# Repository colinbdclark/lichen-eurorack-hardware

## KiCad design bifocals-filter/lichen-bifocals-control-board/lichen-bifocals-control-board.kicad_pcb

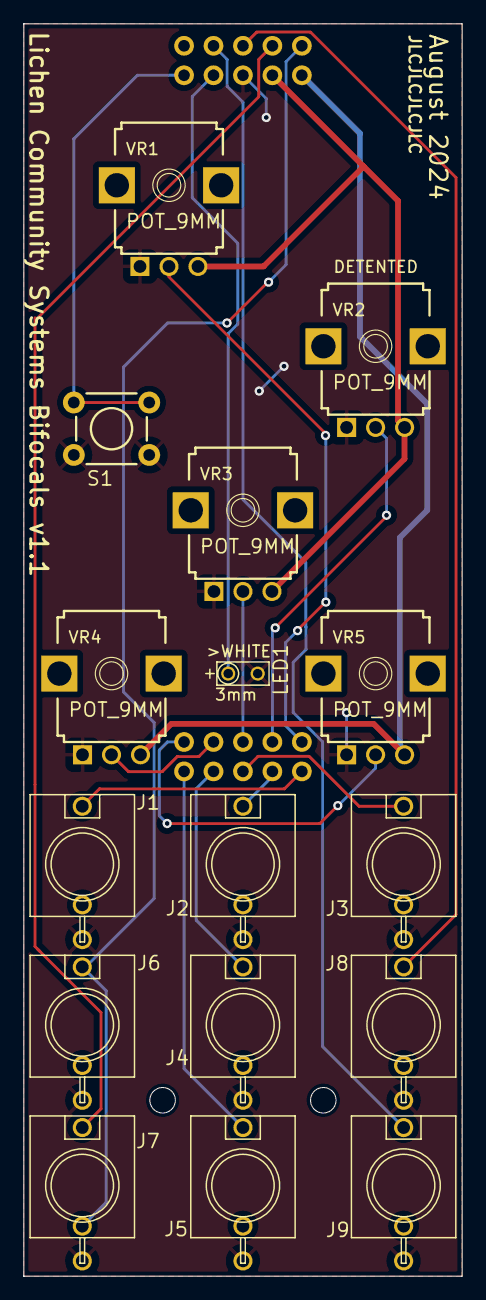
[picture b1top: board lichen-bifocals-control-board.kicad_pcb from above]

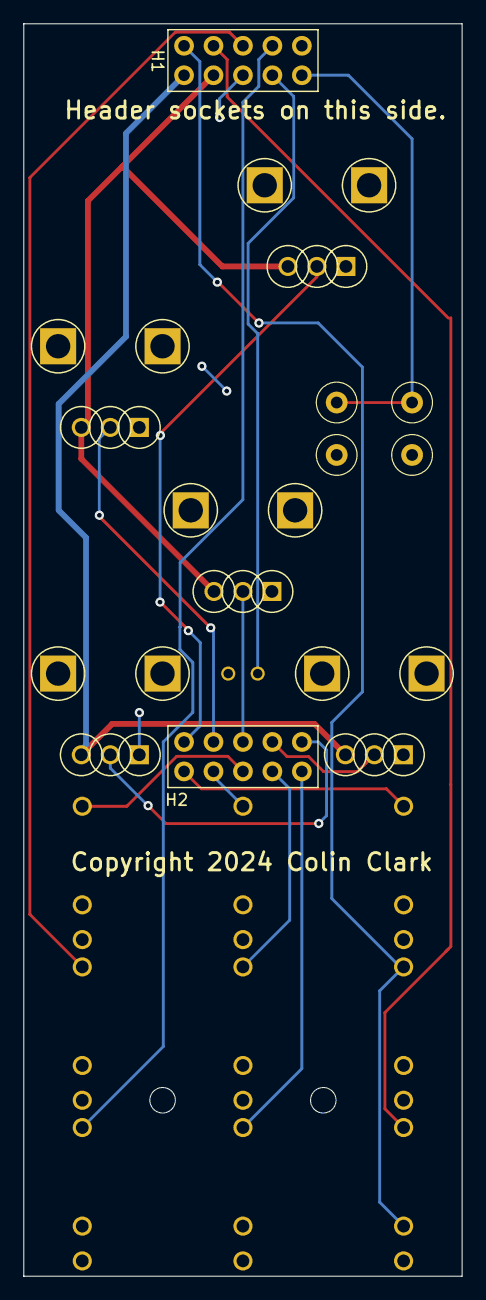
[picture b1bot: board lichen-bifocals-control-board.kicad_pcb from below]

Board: 2 copper layers, 37.8 x 108.0 mm, 20 parts (2 on the bottom side), 19 nets.

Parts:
H1, H2: PIN_HEADER_2x5; Pins_2x05_2.54mm_TH
J1, J2, J3, J4, J5, J6, J7, J8, J9: EURO_JACK; S_JACK
LED1: LED
MH2, MH2#2: MountingHole_2.2mm_M2
S1: TAC_SWITCH_PTH; TL1105SPF250Q_SILK
VR1, VR2, VR3, VR4, VR5: POT_9MM; 9MM_SNAP-IN_POT_SILK

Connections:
+3.3V: H1.1, VR4.3, VR5.3
+5V: H1.3, VR1.3, VR2.3, VR3.3
AUDIO_IN_L: H1.2, J6.TIP, J7.NORM
AUDIO_IN_R: H1.4, J7.TIP
AUDIO_OUT_L: H1.6, J8.TIP
AUDIO_OUT_R: H1.8, J9.TIP
BUTTON: H1.9, S1.1, S1.2
GND: H1.5, J1.GND, J2.GND, J3.GND, J4.GND, J5.GND, J6.GND, J7.GND, J8.GND, J9.GND, LED1.K (C), S1.3, S1.4, VR1.1, VR2.1, VR3.1, VR4.1, VR5.1
JACK_CV_1: H2.1, J1.TIP
JACK_CV_2: H2.3, J2.TIP
JACK_CV_3: H2.5, J3.TIP
JACK_CV_4: H2.7, J4.TIP
JACK_CV_5: H2.9, J5.TIP
LED_CV_OUT: H1.7, LED1.A
POT_1_CV_6: H2.2, VR1.2
POT_2_CV_7: H2.4, VR2.2
POT_3_CV_8: H2.6, VR3.2
POT_4_CV_9: H2.8, VR4.2
POT_5_CV_10: H2.10, VR5.2

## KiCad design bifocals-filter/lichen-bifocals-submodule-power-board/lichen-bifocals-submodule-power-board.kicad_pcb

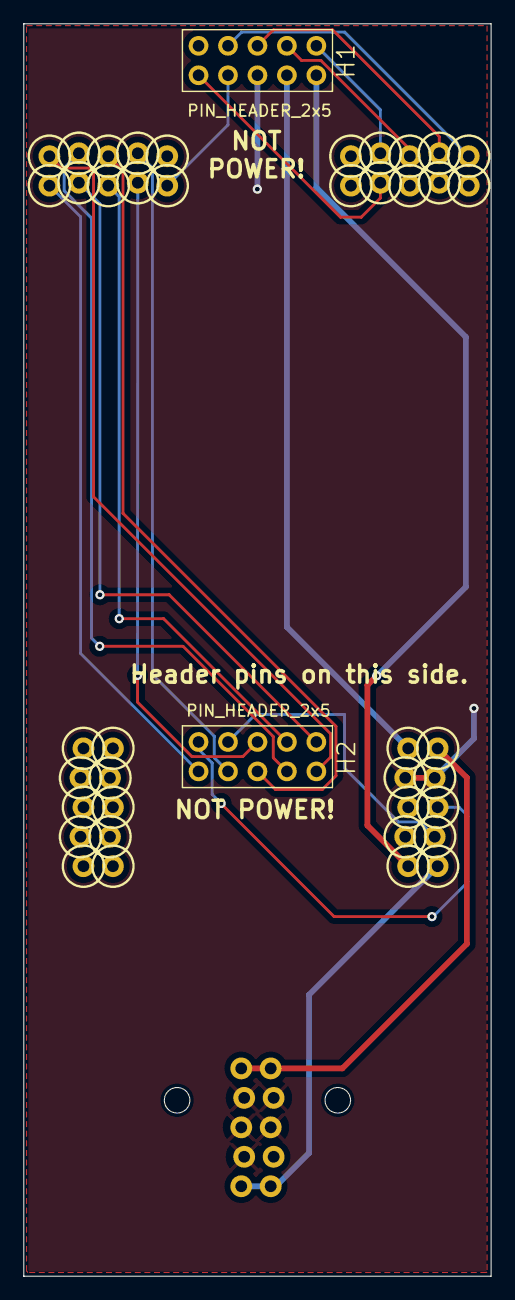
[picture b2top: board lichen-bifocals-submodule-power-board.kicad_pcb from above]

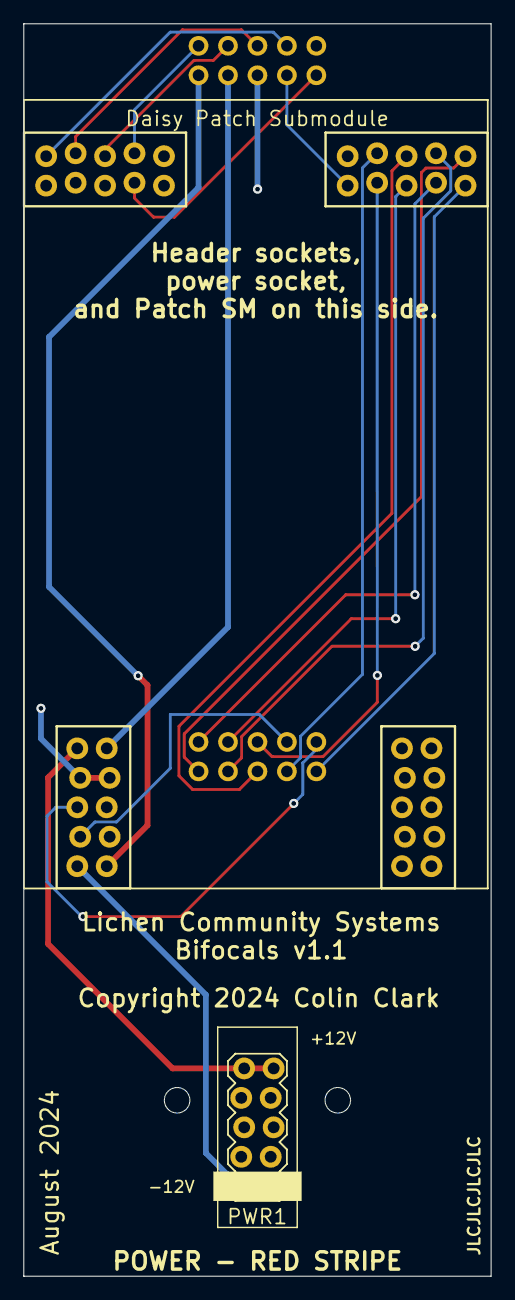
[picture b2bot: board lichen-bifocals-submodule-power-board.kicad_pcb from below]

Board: 2 copper layers, 40.3 x 108.0 mm, 6 parts (3 on the bottom side), 21 nets.

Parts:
H1, H2: PIN_HEADER_2x5; Pins_2x05_2.54mm_TH
MCU1: Daisy Patch Submodule; Daisy_Patch_Submodule
MH1, MH2: MountingHole_2.2mm_M2
PWR1: EURORACK_POWERSHROUD; EURORACK_POWER_SHROUD_LOCK

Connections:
+3.3V: H1.1, MCU1.A10 (+3V3)
+5V: H1.3, MCU1.A6 (+5V)
+12V: MCU1.A5 (+12V), PWR1.POS1, PWR1.POS2
-12V: MCU1.A1 (-12V), PWR1.NEG1, PWR1.NEG2
AUDIO_IN_L: H1.2, MCU1.B4 (AUDIO_IN_L)
AUDIO_IN_R: H1.4, MCU1.B3 (AUDIO_IN_R)
AUDIO_OUT_L: H1.6, MCU1.B2 (AUDIO_OUT_L)
AUDIO_OUT_R: H1.8, MCU1.B1 (AUDIO_OUT_R)
BUTTON: H1.9, MCU1.B7 (I2C1_SCL)
GND: H1.5, MCU1.A4 (GND), MCU1.A7 (GND), PWR1.GND1 (GND), PWR1.GND2 (GND), PWR1.GND3 (GND), PWR1.GND4 (GND), PWR1.GND5 (GND)
JACK_CV_1: H2.1, MCU1.C5 (CV1)
JACK_CV_2: H2.3, MCU1.C4 (CV2)
JACK_CV_3: H2.5, MCU1.C3 (CV3)
JACK_CV_4: H2.7, MCU1.C2 (CV4)
JACK_CV_5: H2.9, MCU1.C6 (CV5)
LED_CV_OUT: H1.7, MCU1.C10 (CV_OUT_1)
POT_1_CV_6: H2.2, MCU1.C7 (CV6)
POT_2_CV_7: H2.4, MCU1.C8 (CV7)
POT_3_CV_8: H2.6, MCU1.C9 (CV8)
POT_4_CV_9: H2.8, MCU1.A2 (UART_RX)
POT_5_CV_10: H2.10, MCU1.A3 (UART_TX)

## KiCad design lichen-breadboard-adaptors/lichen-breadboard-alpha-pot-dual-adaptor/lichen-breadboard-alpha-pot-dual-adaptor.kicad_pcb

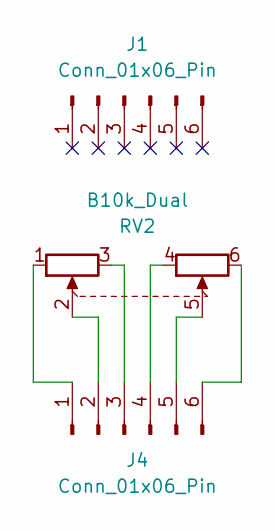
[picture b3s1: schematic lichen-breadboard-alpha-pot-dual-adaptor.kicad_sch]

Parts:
J1, J4: Conn_01x06_Pin; PinHeader_1x06_P2.54mm_Vertical
RV2: B10k_Dual; Potentiometer_Alpha_RD902F-40-00D_Dual_Vertical; Part Number RD90F-40

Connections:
unnamed: J4.1, RV2.1
unnamed: J4.2, RV2.2
unnamed: J4.3, RV2.3
unnamed: J4.4, RV2.4
unnamed: J4.5, RV2.5
unnamed: J4.6, RV2.6

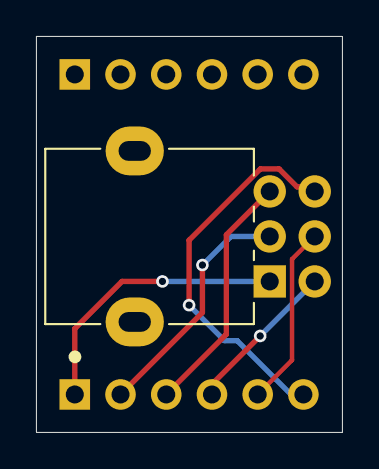
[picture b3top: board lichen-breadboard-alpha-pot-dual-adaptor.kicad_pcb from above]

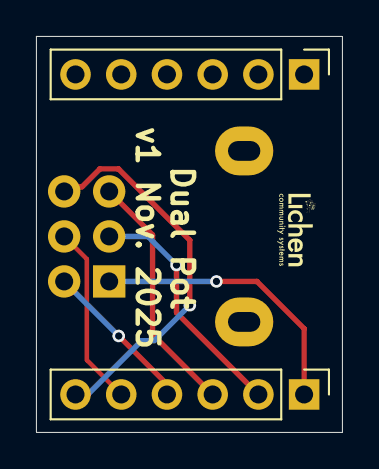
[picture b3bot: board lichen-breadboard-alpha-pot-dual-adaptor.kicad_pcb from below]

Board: 2 copper layers, 17.0 x 22.0 mm, 3 parts (2 on the bottom side), 6 nets.

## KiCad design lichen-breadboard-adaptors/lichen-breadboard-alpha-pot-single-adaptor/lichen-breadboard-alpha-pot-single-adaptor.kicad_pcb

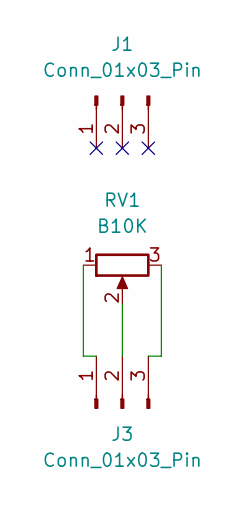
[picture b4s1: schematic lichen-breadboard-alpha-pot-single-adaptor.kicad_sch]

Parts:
J1, J3: Conn_01x03_Pin; PinHeader_1x03_P2.54mm_Vertical
RV1: B10K; Potentiometer_Alpha_RD901_Eurorack; Part Number RD901F-40

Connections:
unnamed: J3.1, RV1.1
unnamed: J3.2, RV1.2
unnamed: J3.3, RV1.3

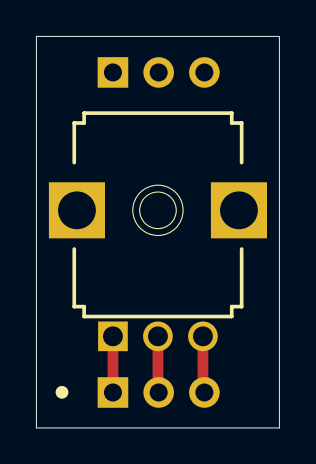
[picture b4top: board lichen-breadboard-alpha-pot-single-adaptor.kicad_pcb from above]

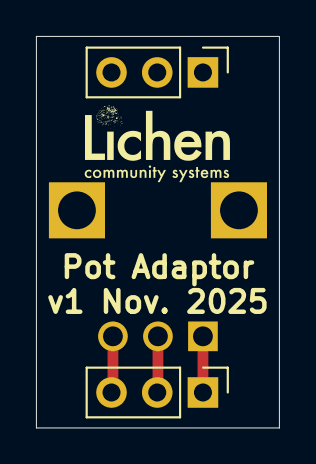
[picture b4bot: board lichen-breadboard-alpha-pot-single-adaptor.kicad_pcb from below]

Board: 2 copper layers, 13.5 x 21.8 mm, 3 parts (2 on the bottom side), 3 nets.

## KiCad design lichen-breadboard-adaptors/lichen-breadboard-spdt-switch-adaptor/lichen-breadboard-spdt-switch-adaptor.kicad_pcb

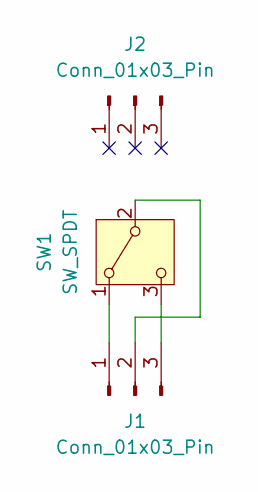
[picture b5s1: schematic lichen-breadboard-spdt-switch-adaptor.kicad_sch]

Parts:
J1, J2: Conn_01x03_Pin; PinHeader_1x03_P2.54mm_Vertical
SW1: SW_SPDT; Miniature_Switch_SPDT_2.54MM

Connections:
unnamed: J1.1, SW1.1 (A)
unnamed: J1.2, SW1.2 (B)
unnamed: J1.3, SW1.3 (C)

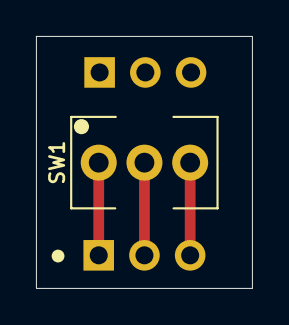
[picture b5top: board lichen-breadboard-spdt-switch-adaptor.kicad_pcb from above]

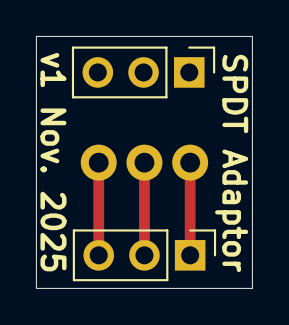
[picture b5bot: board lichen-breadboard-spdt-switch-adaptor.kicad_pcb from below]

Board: 2 copper layers, 12.0 x 14.0 mm, 3 parts (2 on the bottom side), 3 nets.

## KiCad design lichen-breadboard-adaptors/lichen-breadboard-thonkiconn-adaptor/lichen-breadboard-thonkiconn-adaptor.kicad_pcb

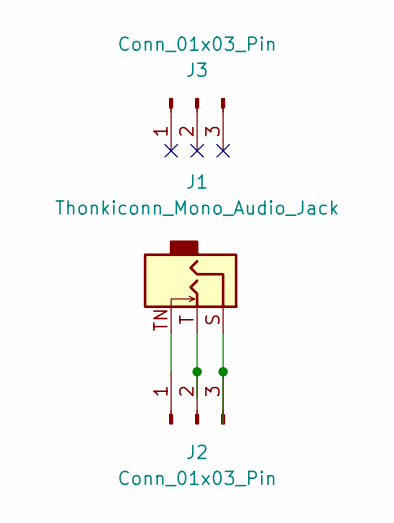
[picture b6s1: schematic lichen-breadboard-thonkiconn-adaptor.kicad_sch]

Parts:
J1: Thonkiconn_Mono_Audio_Jack; Audio_Jack_Thonkiconn_Mono; Part Number WQP518MA/PJ398SM
J2, J3: Conn_01x03_Pin; PinHeader_1x03_P2.54mm_Vertical

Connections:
unnamed: J1.TN, J2.1
unnamed: J1.T, J2.2
unnamed: J1.S, J2.3

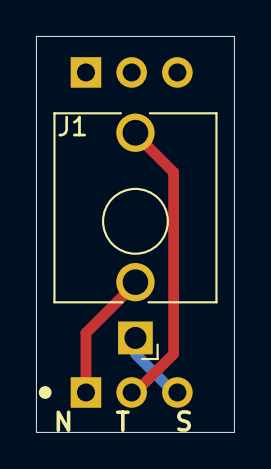
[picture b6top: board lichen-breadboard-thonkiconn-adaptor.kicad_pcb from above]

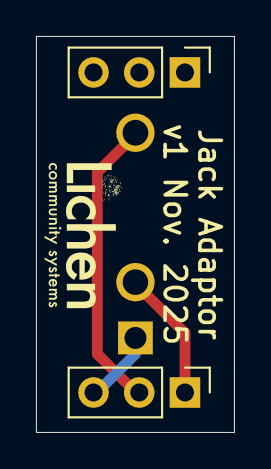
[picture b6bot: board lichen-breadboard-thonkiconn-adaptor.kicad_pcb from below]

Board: 2 copper layers, 11.0 x 22.0 mm, 3 parts (2 on the bottom side), 3 nets.

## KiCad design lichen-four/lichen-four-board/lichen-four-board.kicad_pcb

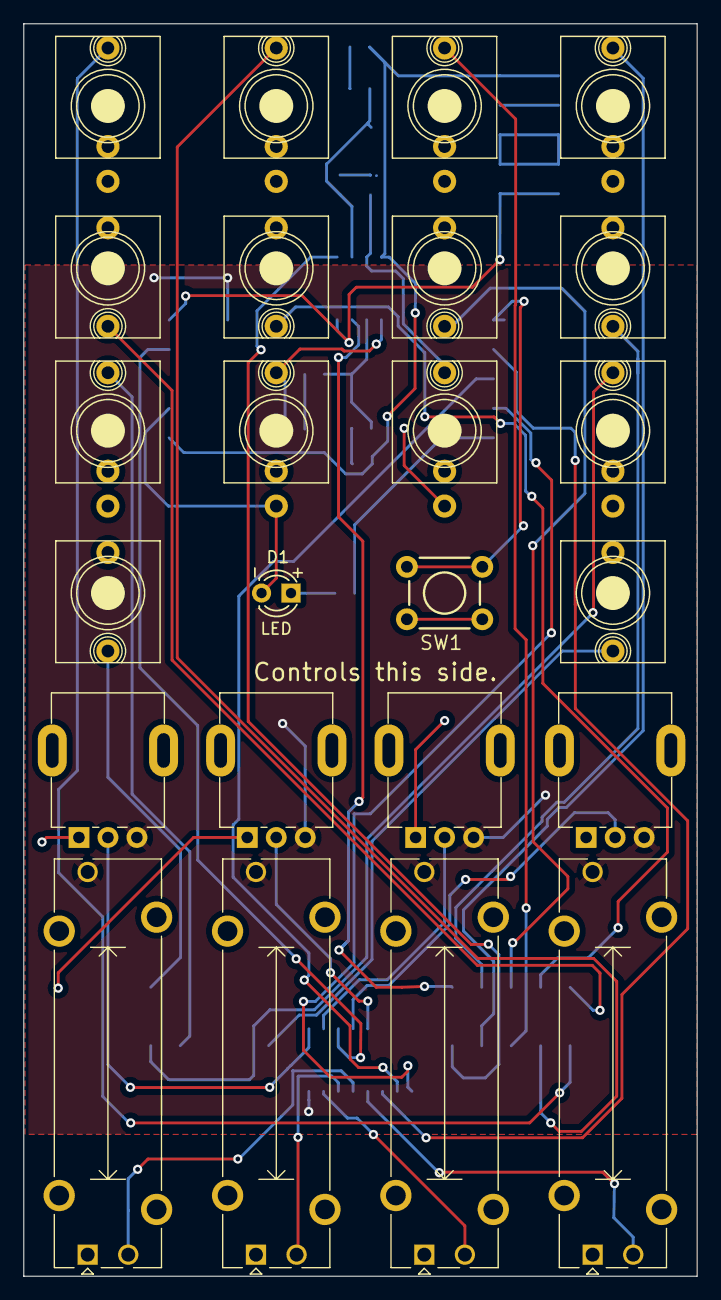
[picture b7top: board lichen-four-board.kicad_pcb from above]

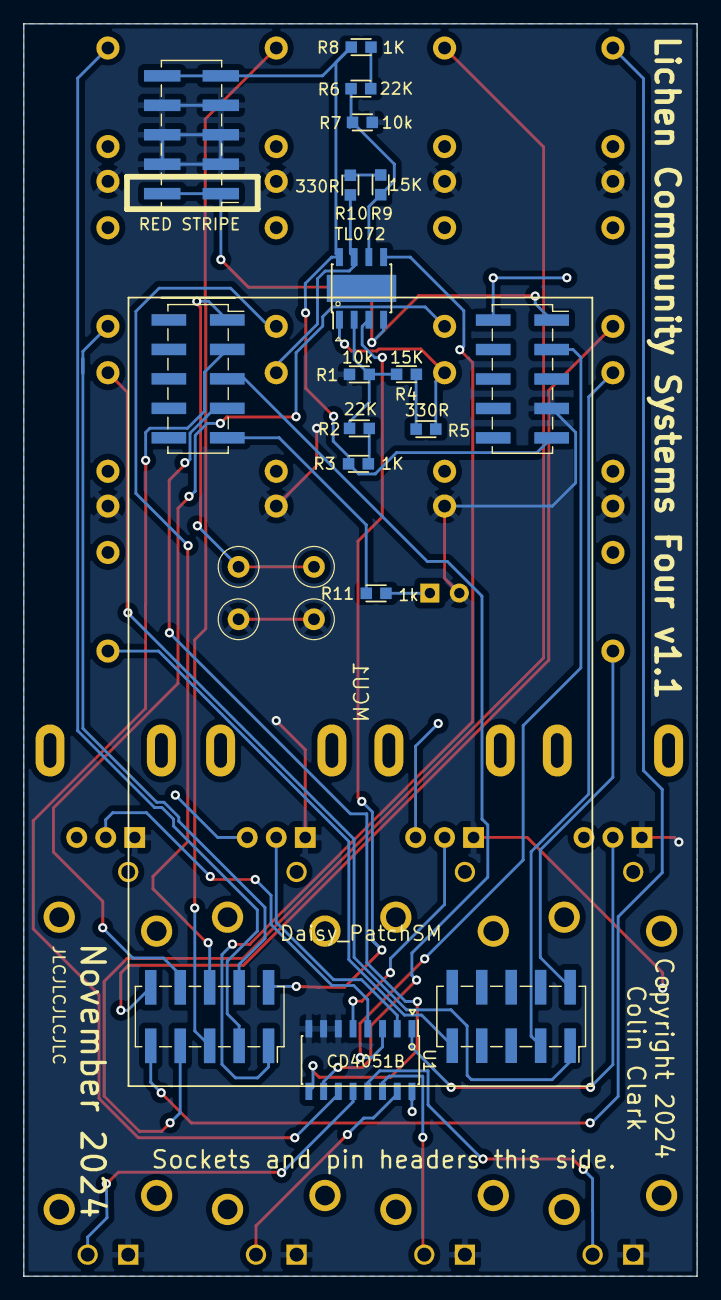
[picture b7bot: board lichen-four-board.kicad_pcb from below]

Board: 2 copper layers, 58.1 x 108.0 mm, 39 parts (14 on the bottom side), 41 nets.

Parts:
D1: LED; LED_3mm_C1A2_Polarity_Indicator
J1, J2, J3, J4, J9, J10, J11, J12: Eurorack_Mono_Jack; AudioJack_WQP518MA
J5, J6, J7, J8, J13, J14: Eurorack_Mono_Jack; AudioJack_WQP518MA_No_S
MCU1: Daisy_PatchSM; Daisy_Patch_Submodule_SMD
PWR1: Eurorack_Power; PinHeader_2x05_P2.54mm_Vertical_SMD
R1, R6: 10k; R_0603
R2, R7: 22K; R_0603
R3, R8: 1K; R_0603
R4, R9: 15K; R_0603
R5, R10: 330R; R_0603
R11: 1k; R_0603
RV1, RV2, RV3, RV4: R_Potentiometer; Potentiometer_Bourns_PTA2043_Single_Slide
RV5, RV6, RV7, RV8: Eurorack_Pot; Potentiometer_Alpha_R0904N
SW1: TL1105SPF250Q; TL1105SPF250Q_SILK
U1: CD4051B; SOIC-16_3.9x9.9mm_Pitch1.27mm
U2: TL072; SOIC-8-1EP_3.9x4.9mm_Pitch1.27mm_HandSolder

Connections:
+3.3V: MCU1.A10 (+3V3), RV1.3, RV2.3, RV3.3, RV4.3, RV5.3, RV6.3, RV7.3, RV8.3, U1.16 (VDD)
+12V: MCU1.A5 (+12V), PWR1.9 (+12V), PWR1.10 (+12V), R3.2, R8.2, U2.8 (V+)
-12V: MCU1.A1 (-12V), PWR1.1 (-12V), PWR1.2 (-12V), U2.4 (V-)
ADC_MUX: MCU1.A2 (UART_RX), U1.3 (X)
AUDIO_CV_OUT_1: J9.T (Tip), MCU1.B2 (AUDIO_OUT_L)
AUDIO_CV_OUT_2: J12.T (Tip), MCU1.B1 (AUDIO_OUT_R)
BIPOLAR_CV_OUT_1: J10.T (Tip), R5.2, U2.1
BIPOLAR_CV_OUT_2: J11.T (Tip), R10.2, U2.7
CHANNEL_SEL_A: MCU1.D2 (SDMMC_D3), U1.11 (A)
CHANNEL_SEL_B: MCU1.D3 (SDMMC_D2), U1.10 (B)
CHANNEL_SEL_C: MCU1.D4 (SDMMC_D1), U1.9 (C)
CV_JACK_1: J1.T (Tip), MCU1.C5 (CV1)
CV_JACK_2: J2.T (Tip), MCU1.C4 (CV2)
CV_JACK_3: J3.T (Tip), MCU1.C3 (CV3)
CV_JACK_4: J4.T (Tip), MCU1.C2 (CV4)
CV_JACK_5: J5.T (Tip), MCU1.C6 (CV5)
CV_JACK_6: J6.T (Tip), MCU1.C7 (CV6)
CV_JACK_7: J7.T (Tip), MCU1.C8 (CV7)
CV_JACK_8: J8.T (Tip), MCU1.C9 (CV8)
GATE_IN_1: J13.T (Tip), MCU1.B10 (GATE_IN_1)
GATE_OUT_1: J14.T (Tip), MCU1.B5 (GATE_OUT_1)
GND: D1.1 (K), J1.S (Sleeve), J2.S (Sleeve), J3.S (Sleeve), J4.S (Sleeve), J9.S (Sleeve), J10.S (Sleeve), J11.S (Sleeve), J12.S (Sleeve), MCU1.A4 (GND), PWR1.3 (GND), PWR1.4 (GND), PWR1.5 (GND), PWR1.6 (GND), PWR1.7 (GND), PWR1.8 (GND), R1.1, R6.1, RV1.1, RV2.1, RV3.1, RV4.1, RV5.1, RV6.1, RV7.1, RV8.1, SW1.3, SW1.4, U1.6 (INH), U1.7 (VEE), U1.8 (VSS)
GPIO_BUTTON_1: MCU1.D1 (SPI_NSS), SW1.1, SW1.2
GPIO_LED_1: MCU1.D5 (SDMMC_D0), R11.2
unnamed: D1.2 (A), R11.1
unnamed: R2.2, R3.1
unnamed: R4.2, R5.1
unnamed: R7.2, R8.1
unnamed: R9.2, R10.1
unnamed: RV1.2, U1.13 (X0)
unnamed: RV2.2, U1.14 (X1)
unnamed: RV3.2, U1.15 (X2)
unnamed: RV4.2, U1.12 (X3)
unnamed: RV5.2, U1.1 (X4)
unnamed: RV6.2, U1.5 (X5)
unnamed: RV7.2, U1.2 (X6)
unnamed: RV8.2, U1.4 (X7)
unnamed: R1.2, R2.1, R4.1, U2.2 (-)
unnamed: R6.2, R7.1, R9.1, U2.6 (-)
UNIPOLAR_CV_OUT_1: MCU1.C10 (CV_OUT_1), U2.3 (+)
UNIPOLAR_CV_OUT_2: MCU1.C1 (CV_OUT_2), U2.5 (+)

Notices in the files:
bifocals-filter/lichen-bifocals-control-board/lichen-bifocals-control-board.kicad_pcb:
Copyright 2024 Colin Clark
